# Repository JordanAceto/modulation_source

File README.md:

# Eurorack Modulation Source

## [SCHEMATIC](https://github.com/JordanAceto/modulation_source/blob/main/main_pcb/construction_docs/modulation_source_schematic.pdf)

## Features:
- Sine and Square wave voltage controlled LFO
- LED indicator shown the LFO speed
- White and Pink noise source
- Sample and Hold
- Convenient normalization
    - LFO square wave normalled to the S&H clock input
    - White noise normalled to the S&H signal input
- There is a pcb front panel, for a cheap and cheerful panel option

## Errata:
- The pink noise gain is a little hot, change R30 to around 39k to bring the pink noise level down if desired

## Status of the project:

Task | Status |
---------|--------------|
Schematic capture | &#9745;
PCB layout | &#9745;
Test build | &#9745;
Safe to order boards| &#9745;

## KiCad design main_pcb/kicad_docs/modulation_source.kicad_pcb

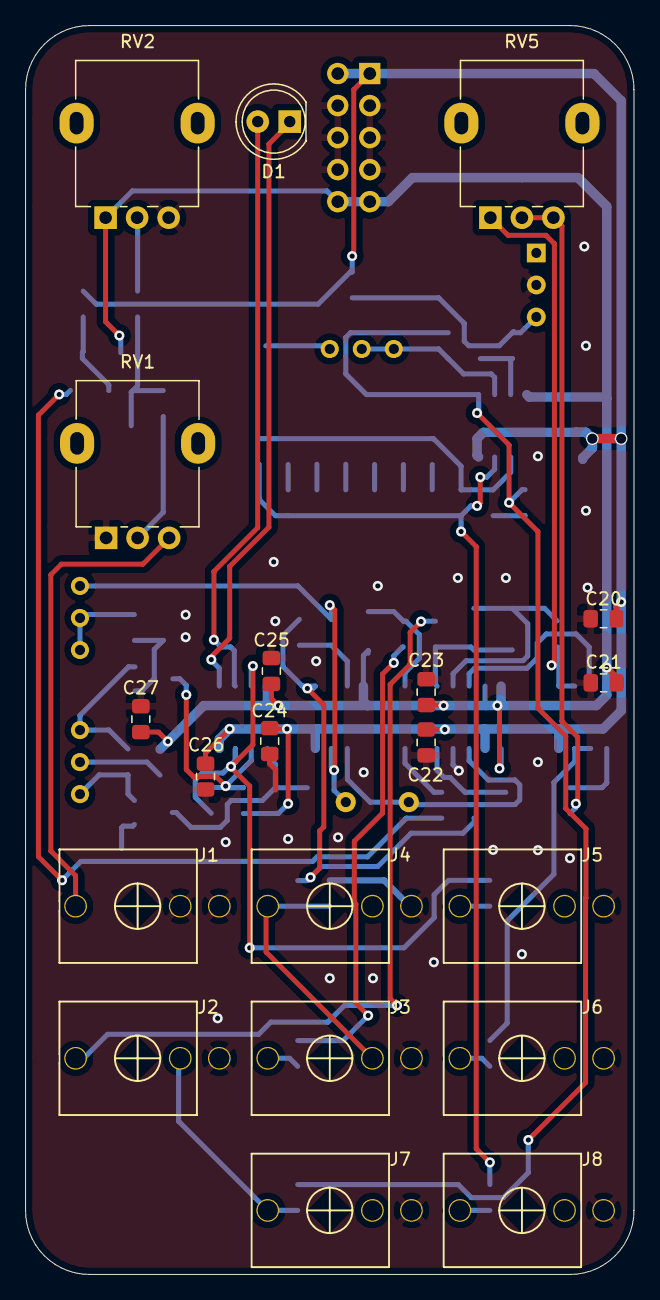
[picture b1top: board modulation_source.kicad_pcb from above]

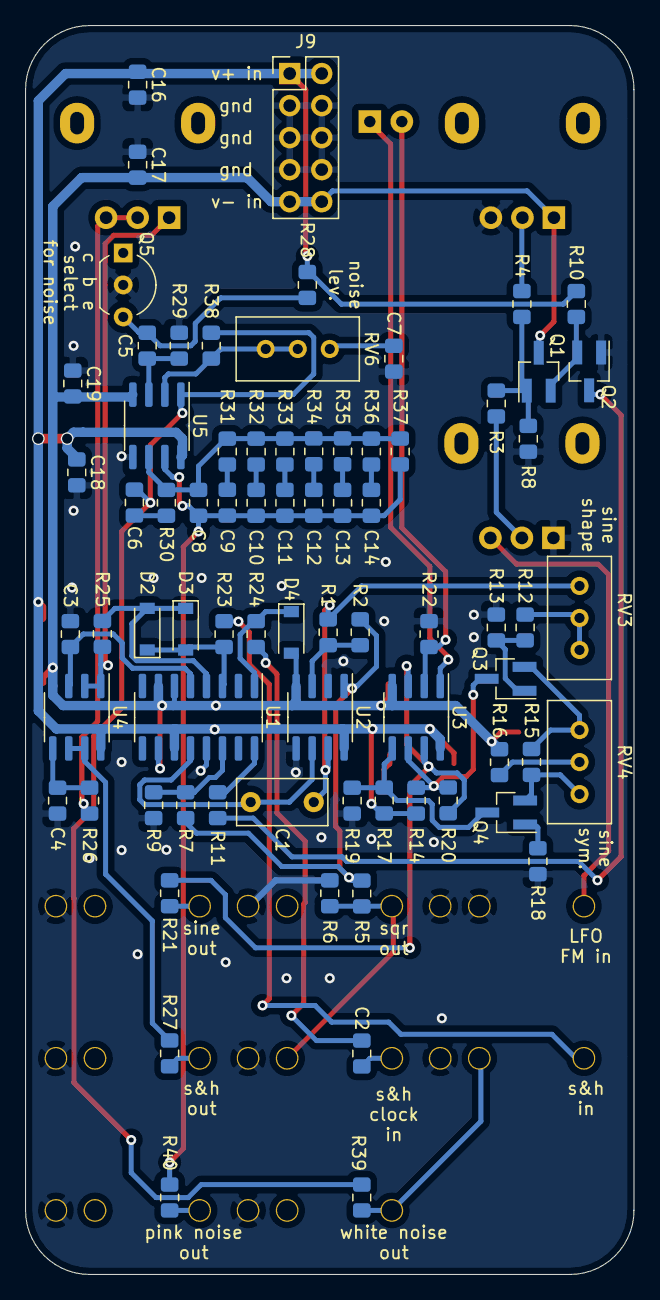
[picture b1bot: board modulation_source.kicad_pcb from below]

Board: 2 copper layers, 48.3 x 99.1 mm, 95 parts (75 on the bottom side), 56 nets.

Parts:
C1: 470nF; C_Rect_L7.0mm_W3.5mm_P5.00mm
C2, C3, C12: 10nF; C_0805_2012Metric_Pad1.15x1.40mm_HandSolder
C4, C14, C18, C19, C20, C21, C22, C23, C24, C25, C26, C27: 100nF; C_0805_2012Metric_Pad1.15x1.40mm_HandSolder
C5: 47uF; C_0805_2012Metric_Pad1.15x1.40mm_HandSolder
C6, C16, C17: 10uF; C_0805_2012Metric_Pad1.15x1.40mm_HandSolder
C7: 1uF; C_0805_2012Metric_Pad1.15x1.40mm_HandSolder
C8: 100pF; C_0805_2012Metric_Pad1.15x1.40mm_HandSolder
C9: 330pF; C_0805_2012Metric_Pad1.15x1.40mm_HandSolder
C10: 1nF; C_0805_2012Metric_Pad1.15x1.40mm_HandSolder
C11: 3n3; C_0805_2012Metric_Pad1.15x1.40mm_HandSolder
C13: 33nF; C_0805_2012Metric_Pad1.15x1.40mm_HandSolder
D1: red_green_LED; LED_D5.0mm
D2, D3, D4: 1N4148W; D_SOD-123
J1, J2, J3, J4, J5, J6, J7, J8: PJ301M-12
J9: power_in; PinHeader_2x05_P2.54mm_Vertical
Q1, Q2: MMBT3906; SOT-23_Handsoldering
Q3, Q4: MMBT3904; SOT-23_Handsoldering
Q5: BC550; TO-92_Inline_Wide
R1, R3, R34: 100k; R_0805_2012Metric_Pad1.15x1.40mm_HandSolder
R2: 220k; R_0805_2012Metric_Pad1.15x1.40mm_HandSolder
R4: 120k; R_0805_2012Metric_Pad1.15x1.40mm_HandSolder
R5, R6: 2k; R_0805_2012Metric_Pad1.15x1.40mm_HandSolder
R7, R23, R24, R25, R33: 33k; R_0805_2012Metric_Pad1.15x1.40mm_HandSolder
R8, R13, R18: 2k2; R_0805_2012Metric_Pad1.15x1.40mm_HandSolder
R9, R14, R17, R30, R32: 10k; R_0805_2012Metric_Pad1.15x1.40mm_HandSolder
R10, R11: 12k; R_0805_2012Metric_Pad1.15x1.40mm_HandSolder
R12: 27k; R_0805_2012Metric_Pad1.15x1.40mm_HandSolder
R15: 390; R_0805_2012Metric_Pad1.15x1.40mm_HandSolder
R16: 18k; R_0805_2012Metric_Pad1.15x1.40mm_HandSolder
R19, R20: 15k; R_0805_2012Metric_Pad1.15x1.40mm_HandSolder
R21, R26, R27, R39, R40: 1k; R_0805_2012Metric_Pad1.15x1.40mm_HandSolder
R22, R31: 3k3; R_0805_2012Metric_Pad1.15x1.40mm_HandSolder
R28: 150k; R_0805_2012Metric_Pad1.15x1.40mm_HandSolder
R29, R36: 1M; R_0805_2012Metric_Pad1.15x1.40mm_HandSolder
R35: 330k; R_0805_2012Metric_Pad1.15x1.40mm_HandSolder
R37: 1M8; R_0805_2012Metric_Pad1.15x1.40mm_HandSolder
R38: 4M7; R_0805_2012Metric_Pad1.15x1.40mm_HandSolder
RV1, RV2: 100k; Potentiometer_Alpha_RD901F-40-00D_Single_Vertical
RV3, RV4: 50k; Potentiometer_Bourns_3296W_Vertical
RV5: 1MA; Potentiometer_Alpha_RD901F-40-00D_Single_Vertical
RV6: 5k; Potentiometer_Bourns_3296W_Vertical
U1: LM13700; SOIC-16_3.9x9.9mm_P1.27mm
U2, U3, U4, U5: TL072; SOIC-8_3.9x4.9mm_P1.27mm

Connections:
+12V: C16.1, C18.1, C20.1, C22.1, C24.1, C26.1, J9.1, J9.2, R10.1, R14.2, R17.2, R28.1, U1.11, U2.8, U3.8, U4.8, U5.8
-12V: C17.2, C19.2, C21.2, C23.2, C25.2, C27.2, D4.2, J9.9, J9.10, Q1.3, R16.1, RV2.1, U1.6, U1.7, U1.10, U2.4, U3.4, U4.4, U5.4
/LFO/LFO_FM_in: J1.3, RV1.3
/LFO/LFO_sine_out: J5.3, R21.1
/LFO_square_out: J3.2, J4.3, R5.1, R6.1
/noise_source/pink_noise_out: J8.3, R40.1
/noise_source/white_noise: C6.2, R38.1, R39.2, U5.1
/sample_and_hold/clock_in: C2.2, J3.3
/sample_and_hold/signal_in: J2.3, R23.2
/sample_and_hold/signal_out: J6.3, R27.1
/white_noise_out: J2.2, J7.3, R39.1
GND: C3.1, C4.2, C7.2, C16.2, C17.1, C18.2, C19.1, C20.2, C21.1, C22.2, C23.1, C24.2, C25.1, C26.2, C27.1, J1.1, J1.2, J2.1, J3.1, J4.1, J5.1, J6.1, J7.1, J8.1, J9.3, J9.4, J9.5, J9.6, J9.7, J9.8, Q2.1, Q5.2, R6.2, R8.2, R9.2, R13.1, R18.1, R19.1, R22.1, R29.1, RV1.1, RV2.3, U1.13, U2.2, U2.5, U5.5
unnamed: C1.1, R1.1, RV3.3, U2.7
unnamed: C1.2, U1.12, U2.6
unnamed: C2.1, R24.2
unnamed: C3.2, U1.5, U4.3
unnamed: C4.1, R26.1, U4.5
unnamed: C5.1, Q5.3, R28.2
unnamed: C5.2, R29.2, U5.3
unnamed: C6.1, R30.2
unnamed: C7.1, RV6.3
unnamed: C8.2, R30.1, R31.2, R32.2, R33.2, R34.2, R35.2, R36.2, R37.2, U5.6
unnamed: C9.2, R31.1
unnamed: C8.1, C9.1, C10.1, C11.1, C12.1, C13.1, C14.1, R37.1, R40.2, U5.7
unnamed: C10.2, R32.1
unnamed: C11.2, R33.1
unnamed: C12.2, R34.1
unnamed: C13.2, R35.1
unnamed: C14.2, R36.1
unnamed: D1.1, U3.1
unnamed: D1.2, R22.2, U3.2
unnamed: D2.1, D3.2, R23.1, U1.3
unnamed: D2.2, D3.1, R25.2, U1.4
unnamed: D4.1, R24.1, U1.1
unnamed: Q1.1, R3.1, R4.1, R8.1
unnamed: Q1.2, Q2.2, R10.2
unnamed: Q2.3, R11.1
unnamed: Q3.1, R12.2, R13.2
unnamed: Q3.2, R15.1, RV4.3
unnamed: Q3.3, R14.1, R20.2, U3.6
unnamed: Q4.1, R18.2
unnamed: Q4.2, R15.2, RV4.1
unnamed: Q4.3, R17.1, R19.2, U3.5
unnamed: R1.2, R2.2, U2.3
unnamed: R2.1, R5.2, R7.2, U2.1
unnamed: R3.2, RV1.2
unnamed: R4.2, RV2.2
unnamed: R7.1, R9.1, U1.14
unnamed: R11.2, U1.16
unnamed: R12.1, RV3.1, RV3.2
unnamed: R16.2, RV4.2
unnamed: R20.1, R21.2, U3.3, U3.7
unnamed: R25.1, RV5.1, U4.1, U4.2
unnamed: R26.2, RV5.2, RV5.3
unnamed: R27.2, U4.6, U4.7
unnamed: R38.2, RV6.1, RV6.2, U5.2

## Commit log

2020-12-12 add some rendered pics of the pcb
2022-01-05 add front panel
2022-01-15 update after successful build

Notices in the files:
main_pcb/kicad_docs/modulation_source.kicad_pcb:
License: CC by 4.0
